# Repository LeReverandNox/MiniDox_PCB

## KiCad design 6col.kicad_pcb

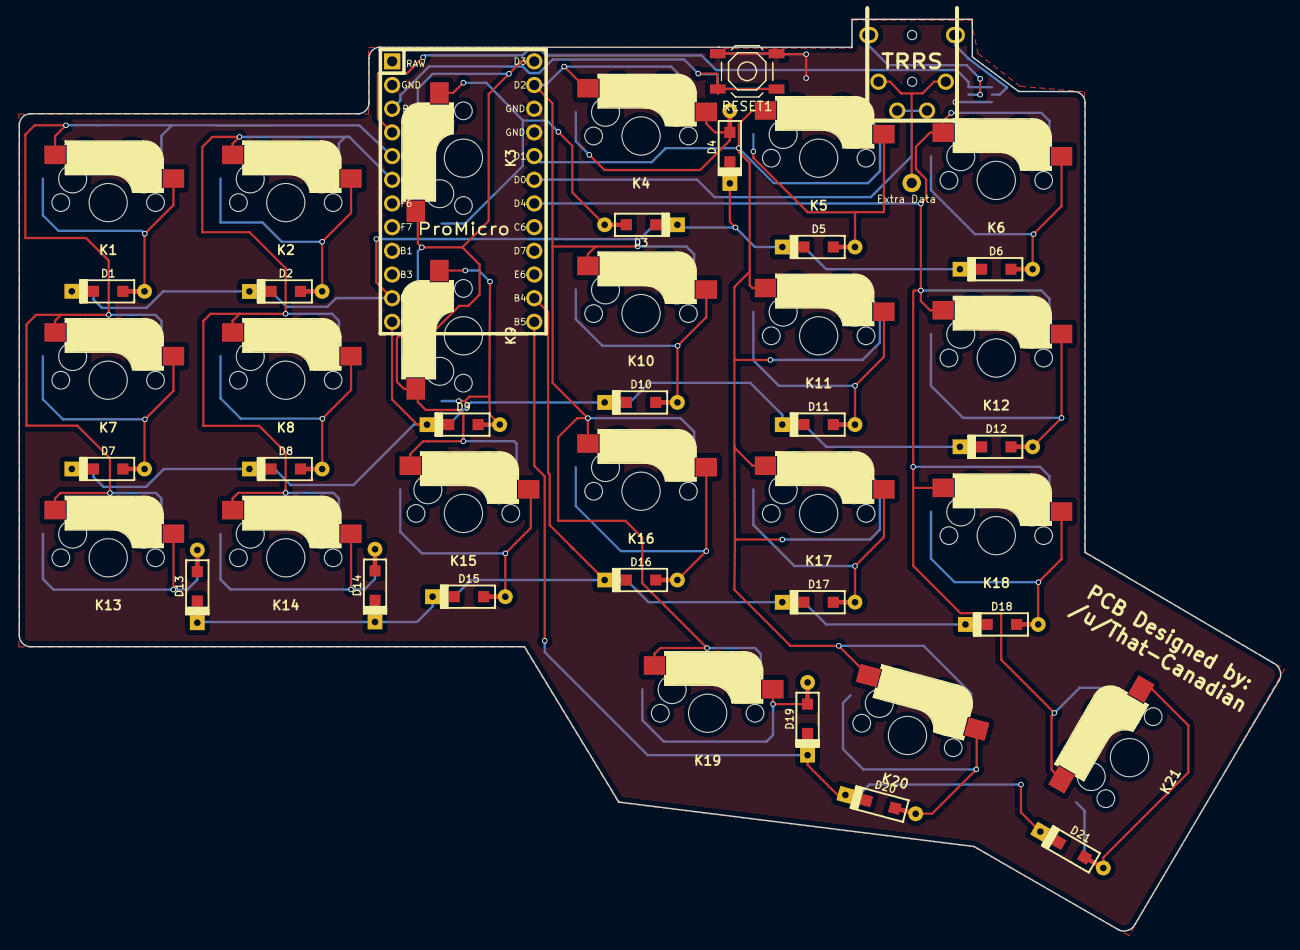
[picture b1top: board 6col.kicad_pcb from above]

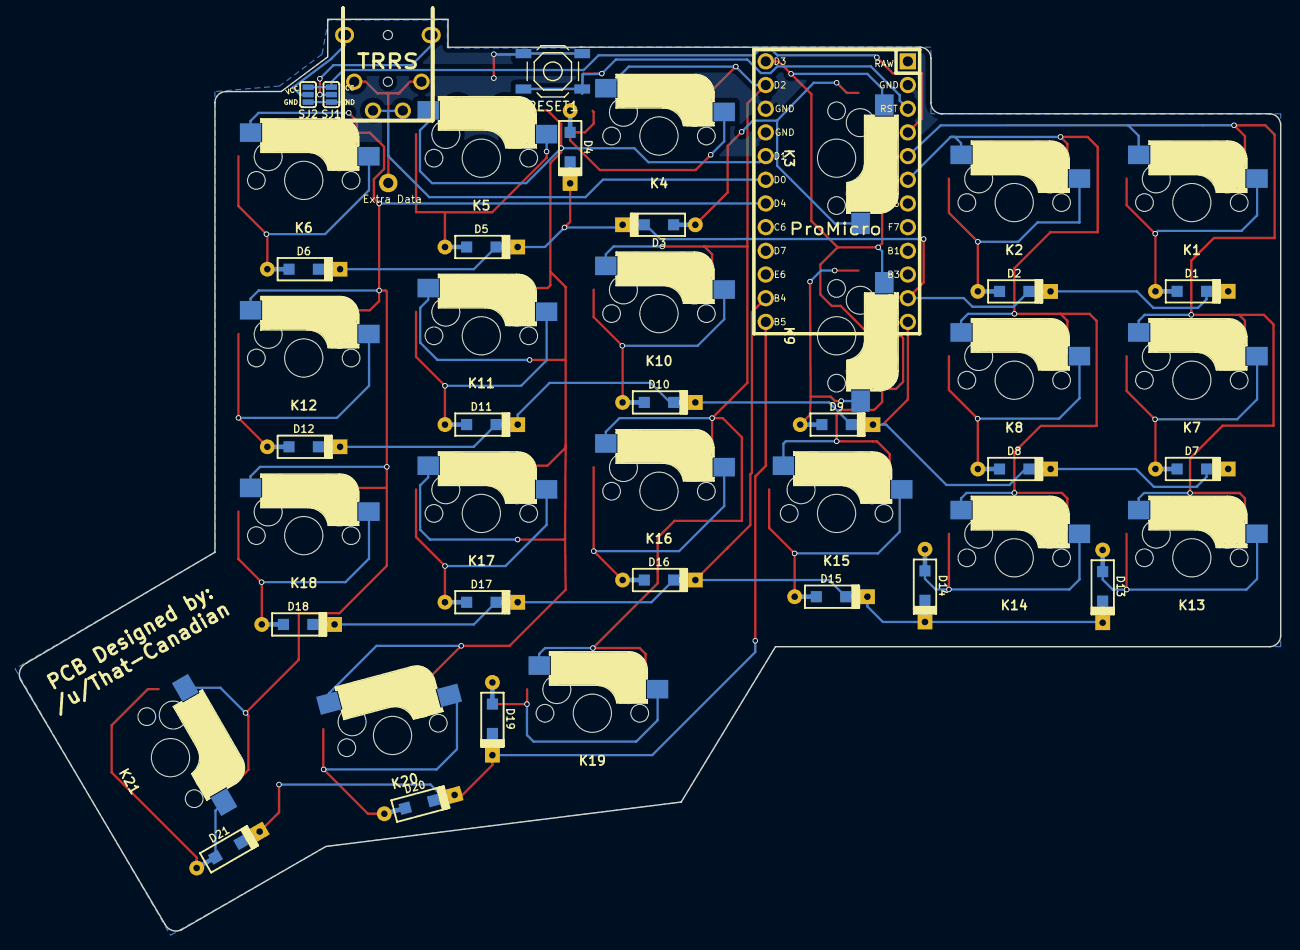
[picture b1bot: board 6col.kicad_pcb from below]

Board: 2 copper layers, 135.3 x 97.8 mm, 48 parts (24 on the bottom side), 37 nets.

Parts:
D1, D2, D3, D4, D5, D6, D7, D8, D9, D10, D11, D12, D13, D14, D15, D16, D17, D18, D19, D20, D21: D; D_SOD123_axial-dual
K1, K2, K3, K4, K5, K6, K7, K8, K9, K10, K11, K12, K13, K14, K15, K16, K17, K18, K19, K20, K21: KAILH_SK; CherryMX_Hotswap_lrn
K22: TRRS; 4pin35mmAudio-dualsided
RESET1, RESET1#2: RESET; SW_SPST_TL3342
SJ1, SJ2: SOLDER_JUMPER_3
U1: ProMicro; Pro_Micro

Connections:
/col1: K1.2, K7.2, K13.2, U1.5
/col2: K2.2, K8.2, K14.2, U1.6
/col3: K3.2, K9.2, K15.2, U1.13
/col4: K4.2, K10.2, K16.2, K19.2, U1.14
/col5: K5.2, K11.2, K17.2, K20.2, U1.17
/col6: K6.2, K12.2, K18.2, K21.2, U1.19
/data: K22.3, U1.18
/row1: D1.1, D2.1, D3.1, D4.1, D5.1, D6.1, U1.11
/row2: D7.1, D8.1, D9.1, D10.1, D11.1, D12.1, U1.12
/row3: D13.1, D14.1, D15.1, D16.1, D17.1, D18.1, U1.23
/row4: D19.1, D20.1, D21.1, U1.24
GND: RESET1.2, RESET1#2.2, SJ1.3, SJ2.3, U1.2, U1.15, U1.16
unnamed: D1.2, K1.1
unnamed: D2.2, K2.1
unnamed: D3.2, K3.1
unnamed: D4.2, K4.1
unnamed: D5.2, K5.1
unnamed: D6.2, K6.1
unnamed: D7.2, K7.1
unnamed: D8.2, K8.1
unnamed: D9.2, K9.1
unnamed: D10.2, K10.1
unnamed: D11.2, K11.1
unnamed: D12.2, K12.1
unnamed: D13.2, K13.1
unnamed: D14.2, K14.1
unnamed: D15.2, K15.1
unnamed: D16.2, K16.1
unnamed: D17.2, K17.1
unnamed: D18.2, K18.1
unnamed: D19.2, K19.1
unnamed: D20.2, K20.1
unnamed: D21.2, K21.1
unnamed: K22.1, SJ2.2
unnamed: K22.4, SJ1.2
unnamed: RESET1.1, RESET1#2.1, U1.3
VCC: SJ1.1, SJ2.1, U1.4

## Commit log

2020-01-22 Fix short on sch between c3 and r3
2020-01-22 Fix sch again
2020-01-22 One more fix on sch
2020-01-22 First version, looks ok
2020-01-22 Add lib, for easy portability
2020-01-23 WIP on Kailh sockets support
2020-01-24 Fix TRRS soldermask and add missing pad
2020-01-25 Add top plate edge cuts
2020-01-25 Add back and front layer
2020-01-25 Add holes in pcb to use standoffs
2020-01-25 Add holes for screws
2020-01-25 Adjust position errors on rotated keys
2020-01-25 Add bottom plate
2020-01-25 Remove useless file
2020-01-25 Rename files
2020-01-26 WIP on new TRRS position
2020-01-26 Add creators
2020-01-27 Front copper layer fix on rotated keys
2020-01-27 Add front copper layer
2020-01-28 Fix top/bottom plates edges
